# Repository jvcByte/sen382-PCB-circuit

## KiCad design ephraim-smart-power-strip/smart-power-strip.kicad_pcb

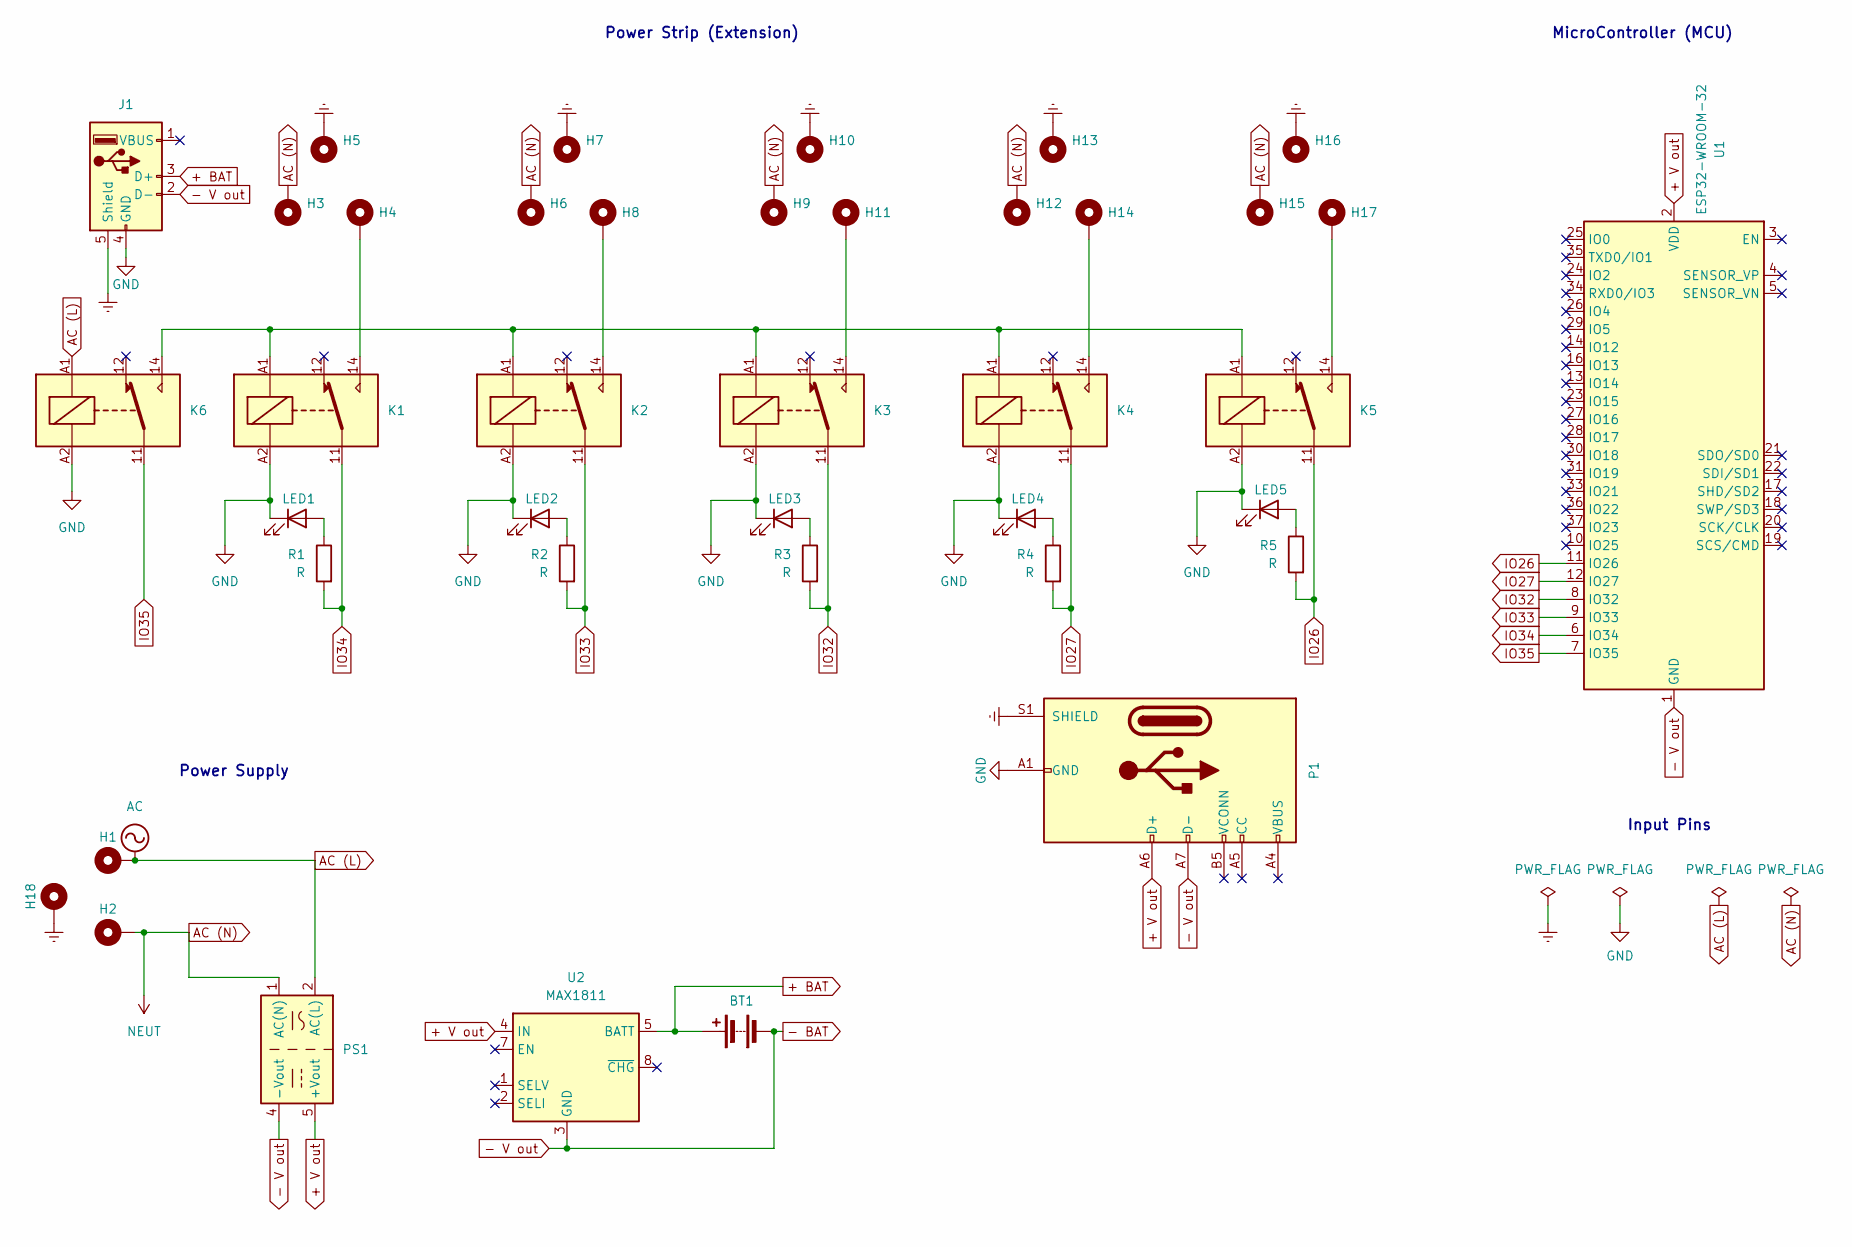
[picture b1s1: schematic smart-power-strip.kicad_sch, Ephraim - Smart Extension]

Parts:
BT1: Battery; BatteryHolder_Keystone_2462_2xAA
H1, H2, H3, H4, H5, H6, H7, H8, H9, H10, H11, H12, H13, H14, H15, H16, H17, H18: MountingHole_Pad; MountingHole_2.2mm_M2_DIN965_Pad
J1: USB_A; USB_A_CNCTech_1001-011-01101_Horizontal
K1, K2, K3, K4, K5, K6: Relay_SPDT; Relay_SPDT_Finder_36.11
LED1, LED2, LED3, LED4, LED5: LED; LED_D4.0mm
P1: USB_C_Plug_USB2.0; USB_C_Plug_Molex_105444
PS1: RAC20-05SK; Converter_ACDC_Recom_RAC20-xxSK_THT
R1, R2, R3, R4, R5: R; R_LDR_4.9x4.2mm_P2.54mm_Vertical
U1: ESP32-WROOM-32
U2: MAX1811; SOIC-8_3.9x4.9mm_P1.27mm

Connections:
+ BAT: BT1.1 (+), J1.3 (D+), U2.5 (BATT)
+ V out: P1.A6 (D+), PS1.5 (+Vout), U1.2 (VDD), U2.4 (IN)
- BAT: BT1.2 (-), J1.2 (D-), P1.A7 (D-), PS1.4 (-Vout), U1.1 (GND), U1.15 (GND), U1.38 (GND), U1.39 (GND), U2.3 (GND), U2.6 (GND)
AC (L): H1.1, K6.A1, PS1.2 (AC(L))
AC (N): H2.1, H3.1, H6.1, H9.1, H12.1, H15.1, PS1.1 (AC(N))
Earth: H5.1, H7.1, H10.1, H13.1, H16.1, H18.1, J1.5 (Shield), P1.S1 (SHIELD)
GND: J1.4 (GND), K1.A2, K2.A2, K3.A2, K4.A2, K5.A2, K6.A2, LED1.1 (K), LED2.1 (K), LED3.1 (K), LED4.1 (K), LED5.1 (K), P1.A1 (GND), P1.A12 (GND), P1.B1 (GND), P1.B12 (GND)
IO26: K5.11, R5.2, U1.11 (IO26)
IO27: K4.11, R4.2, U1.12 (IO27)
IO32: K3.11, R3.2, U1.8 (IO32)
IO33: K2.11, R2.2, U1.9 (IO33)
IO34: K1.11, R1.2, U1.6 (IO34)
IO35: K6.11, U1.7 (IO35)
unnamed: H4.1, K1.14
unnamed: H8.1, K2.14
unnamed: H11.1, K3.14
unnamed: H14.1, K4.14
unnamed: H17.1, K5.14
unnamed: K1.A1, K2.A1, K3.A1, K4.A1, K5.A1, K6.14
unnamed: LED1.2 (A), R1.1
unnamed: LED2.2 (A), R2.1
unnamed: LED3.2 (A), R3.1
unnamed: LED4.2 (A), R4.1
unnamed: LED5.2 (A), R5.1

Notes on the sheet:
Input Pins
MicroController (MCU)
Power Strip (Extension)
Power Supply

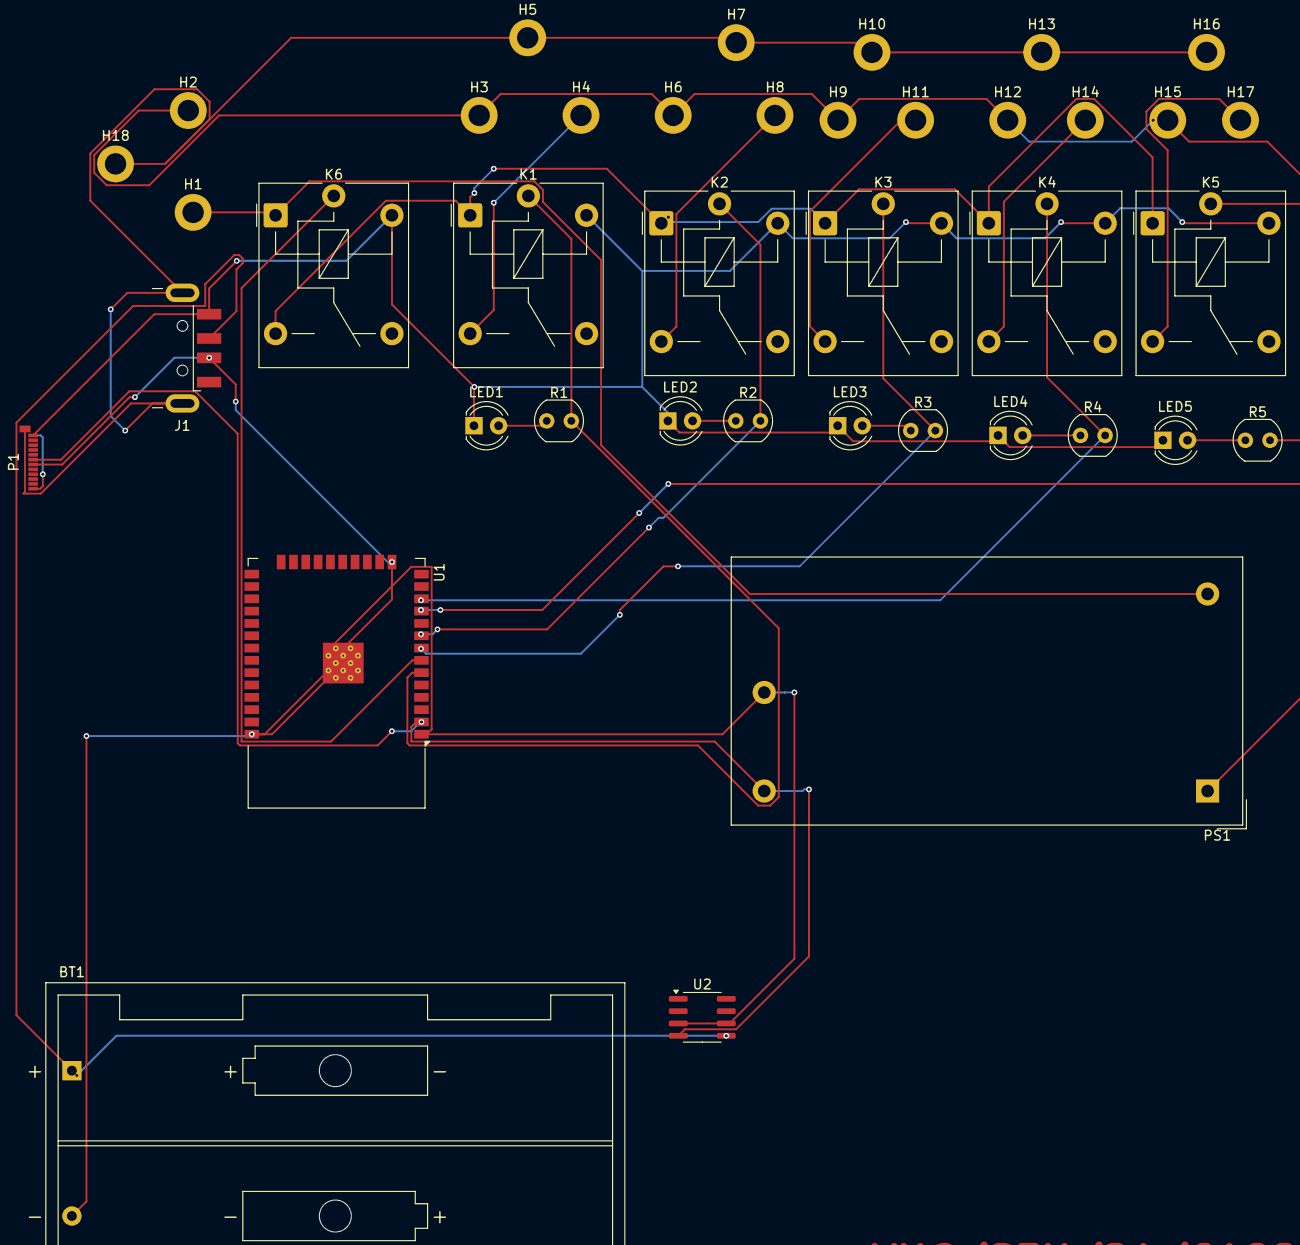
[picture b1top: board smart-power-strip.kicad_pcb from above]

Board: 2 copper layers, 40 parts (0 on the bottom side), 24 nets.

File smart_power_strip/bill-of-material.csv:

"Reference","Value","Footprint","Datasheet","Qty","DNP","Exclude from BOM","Exclude from Board"
"BT1","Battery","Battery:BatteryHolder_Keystone_2462_2xAA","~","1","","",""
"H1,H2,H3,H4,H5,H6,H7,H8,H9,H10,H11,H12,H13,H14,H15,H16,H17,H18","MountingHole_Pad","MountingHole:MountingHole_2.2mm_M2_DIN965_Pad","~","18","","",""
"J1","USB_A","Connector_USB:USB_A_CNCTech_1001-011-01101_Horizontal","~","1","","",""
"K1,K2,K3,K4,K5,K6","Relay_SPDT","Relay_THT:Relay_SPDT_Finder_36.11","~","6","","",""
"LED1,LED2,LED3,LED4,LED5","LED","LED_THT:LED_D4.0mm","~","5","","",""
"P1","USB_C_Plug_USB2.0","Connector_USB:USB_C_Plug_Molex_105444","https://www.usb.org/sites/default/files/documents/usb_type-c.zip","1","","",""
"PS1","RAC20-05SK","Converter_ACDC:Converter_ACDC_Recom_RAC20-xxSK_THT","https://recom-power.com/pdf/Powerline_AC-DC/RAC20-K.pdf","1","","",""
"R1,R2,R3,R4,R5","R","OptoDevice:R_LDR_4.9x4.2mm_P2.54mm_Vertical","~","5","","",""
"U1","ESP32-WROOM-32","RF_Module:ESP32-WROOM-32","https://www.espressif.com/sites/default/files/documentation/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","1","","",""
"U2","MAX1811","Package_SO:SOIC-8_3.9x4.9mm_P1.27mm","https://datasheets.maximintegrated.com/en/ds/MAX1811.pdf","1","","",""

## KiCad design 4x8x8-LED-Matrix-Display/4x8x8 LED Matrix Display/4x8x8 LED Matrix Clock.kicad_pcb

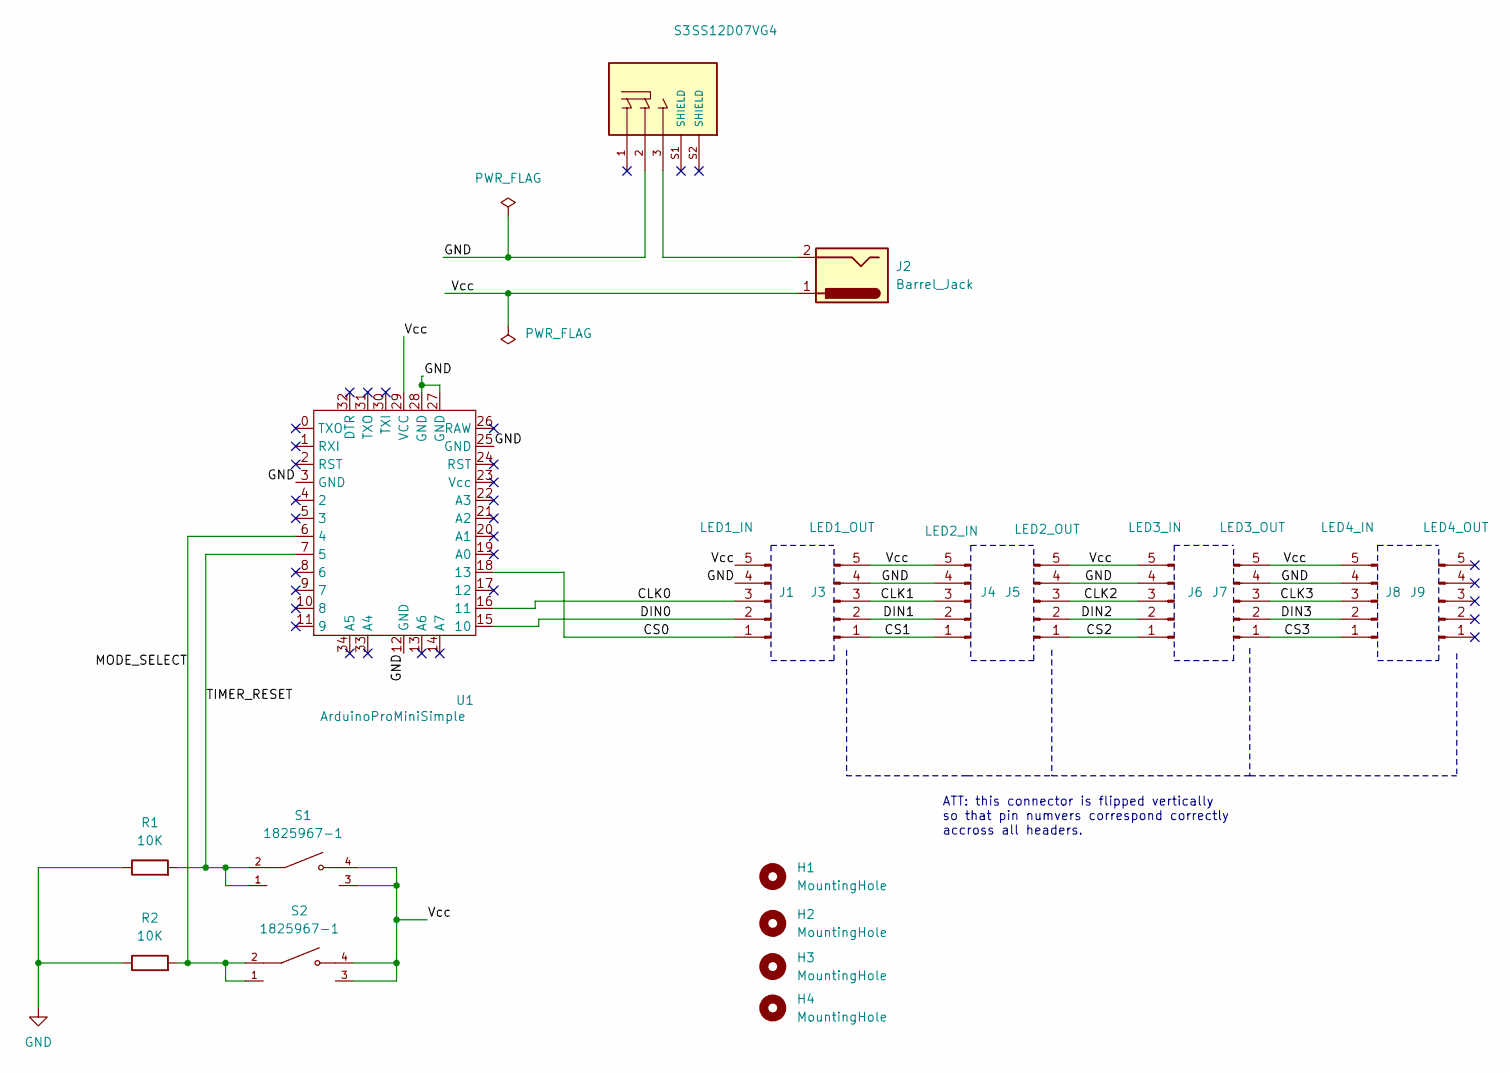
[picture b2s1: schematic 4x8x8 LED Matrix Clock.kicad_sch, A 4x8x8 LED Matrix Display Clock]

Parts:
H1, H2, H3, H4: MountingHole; MountingHole_2.5mm
J1: LED1_IN; PinHeader_1x05_P2.54mm_Vertical
J2: Barrel_Jack; BarrelJack_Horizontal
J3: LED1_OUT; PinHeader_1x05_P2.54mm_Vertical
J4: LED2_IN; PinHeader_1x05_P2.54mm_Vertical
J5: LED2_OUT; PinHeader_1x05_P2.54mm_Vertical
J6: LED3_IN; PinHeader_1x05_P2.54mm_Vertical
J7: LED3_OUT; PinHeader_1x05_P2.54mm_Vertical
J8: LED4_IN; PinHeader_1x05_P2.54mm_Vertical
J9: LED4_OUT; PinHeader_1x05_P2.54mm_Vertical
R1, R2: 10K; R_Axial_DIN0204_L3.6mm_D1.6mm_P7.62mm_Horizontal
S1, S2: 1825967-1; SW_1825967-1
S3: SS12D07VG4; SW_SS12D07VG4; PARTREV 1
U1: ArduinoProMiniSimple; ArduinoProMiniCustom

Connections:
/CLK0: J1.3, U1.16 (11)
/CLK1: J3.3, J4.3
/CLK2: J5.3, J6.3
/CLK3: J7.3, J8.3
/CS0: J1.1, U1.18 (13)
/CS1: J3.1, J4.1
/CS2: J5.1, J6.1
/CS3: J7.1, J8.1
/DIN0: J1.2, U1.15 (10)
/DIN1: J3.2, J4.2
/DIN2: J5.2, J6.2
/DIN3: J7.2, J8.2
/MODE_SELECT: R2.2, S2.1, S2.2, U1.6 (4)
/TIMER_RESET: R1.2, S1.1, S1.2, U1.7 (5)
/Vcc: J1.5, J2.1, J3.5, J4.5, J5.5, J6.5, J7.5, J8.5, S1.3, S1.4, S2.3, S2.4, U1.29 (VCC)
GND: J1.4, J3.4, J4.4, J5.4, J6.4, J7.4, J8.4, R1.1, R2.1, S3.2, U1.3 (GND), U1.12 (GND), U1.25 (GND), U1.27 (GND), U1.28 (GND)
unnamed: J2.2, S3.3

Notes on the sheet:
ATT: this connector is flipped vertically so that pin numvers correspond correctly accross all headers.

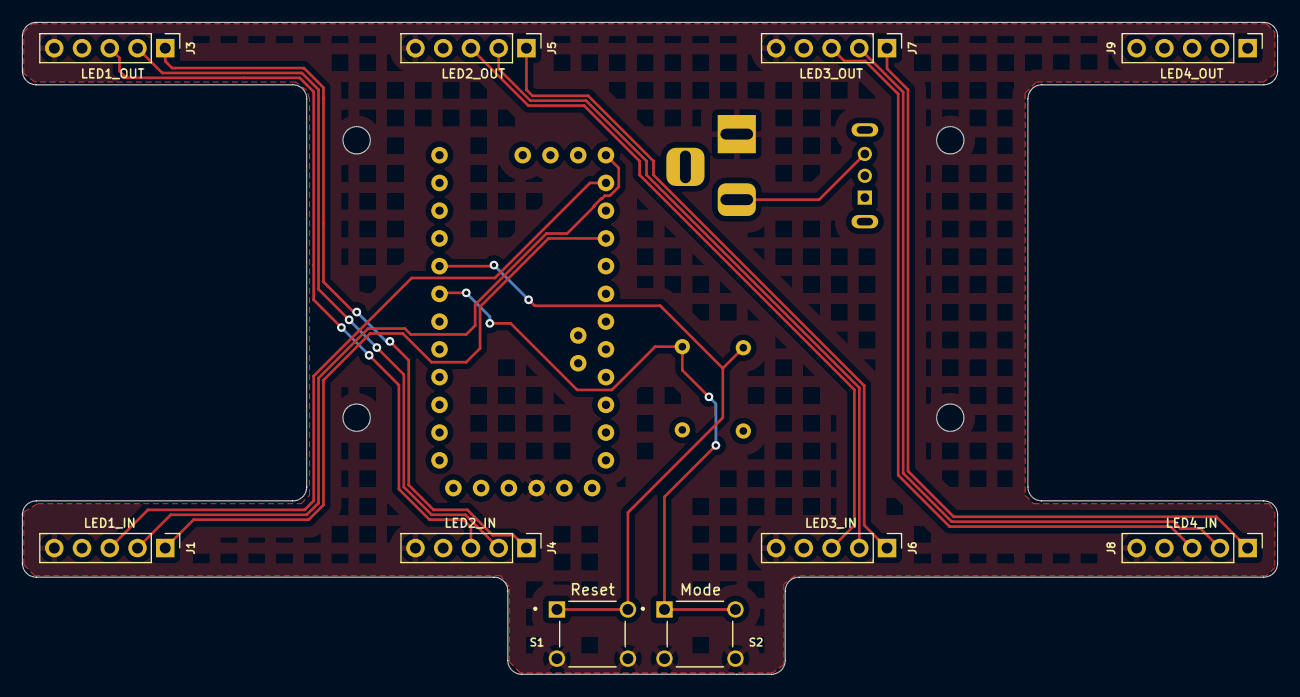
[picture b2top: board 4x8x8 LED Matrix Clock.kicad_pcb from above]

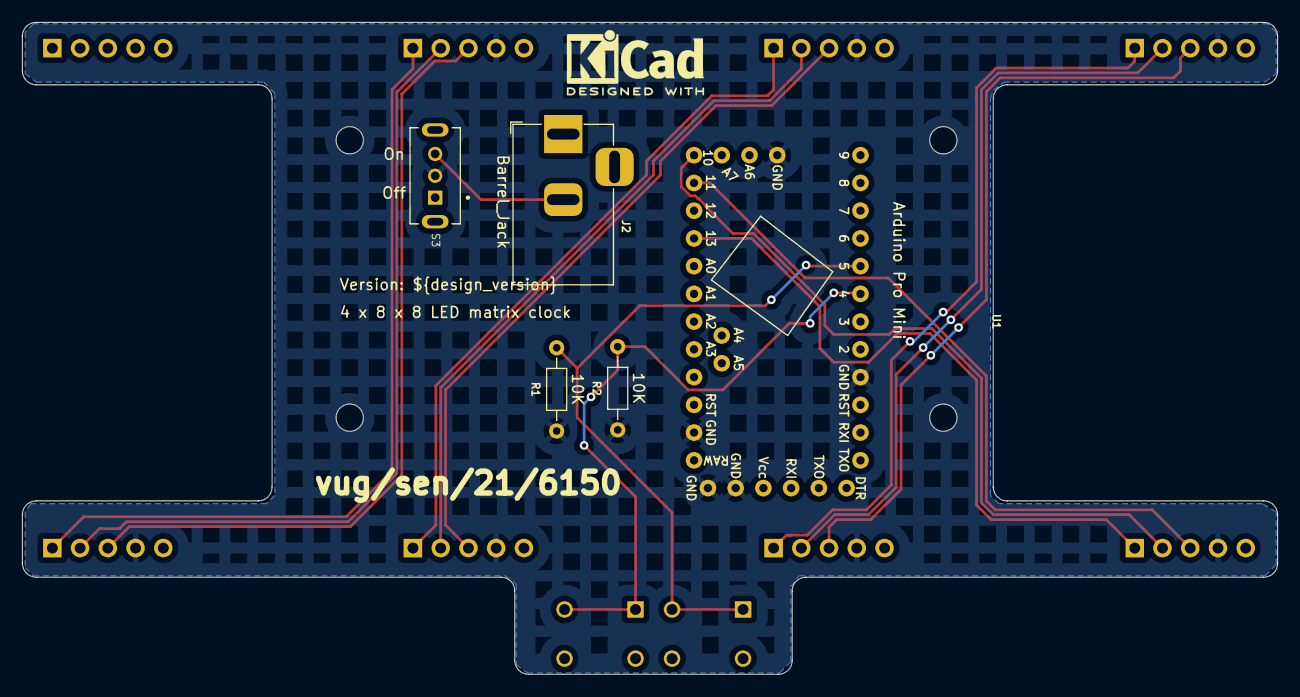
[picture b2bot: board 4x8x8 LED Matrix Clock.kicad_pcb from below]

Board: 2 copper layers, 114.9 x 59.7 mm, 19 parts (5 on the bottom side), 17 nets.

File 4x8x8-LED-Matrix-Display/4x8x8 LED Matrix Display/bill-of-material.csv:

"Reference","Value","Footprint","Datasheet","Qty","DNP","Exclude from BOM","Exclude from Board"
"H1,H2,H3,H4","MountingHole","MountingHole:MountingHole_2.5mm","~","4","","",""
"J1","LED1_IN","Connector_PinHeader_2.54mm:PinHeader_1x05_P2.54mm_Vertical","~","1","","",""
"J2","Barrel_Jack","Connector_BarrelJack:BarrelJack_Horizontal","~","1","","",""
"J3","LED1_OUT","Connector_PinHeader_2.54mm:PinHeader_1x05_P2.54mm_Vertical","~","1","","",""
"J4","LED2_IN","Connector_PinHeader_2.54mm:PinHeader_1x05_P2.54mm_Vertical","~","1","","",""
"J5","LED2_OUT","Connector_PinHeader_2.54mm:PinHeader_1x05_P2.54mm_Vertical","~","1","","",""
"J6","LED3_IN","Connector_PinHeader_2.54mm:PinHeader_1x05_P2.54mm_Vertical","~","1","","",""
"J7","LED3_OUT","Connector_PinHeader_2.54mm:PinHeader_1x05_P2.54mm_Vertical","~","1","","",""
"J8","LED4_IN","Connector_PinHeader_2.54mm:PinHeader_1x05_P2.54mm_Vertical","~","1","","",""
"J9","LED4_OUT","Connector_PinHeader_2.54mm:PinHeader_1x05_P2.54mm_Vertical","~","1","","",""
"R1,R2","10K","Resistor_THT:R_Axial_DIN0204_L3.6mm_D1.6mm_P7.62mm_Horizontal","~","2","","",""
"S1,S2","1825967-1","1825967-1:SW_1825967-1","","2","","",""
"S3","SS12D07VG4","SS12D07VG4:SW_SS12D07VG4","","1","","",""
"U1","ArduinoProMiniSimple","DesktopLibrary:ArduinoProMiniCustom","","1","","",""

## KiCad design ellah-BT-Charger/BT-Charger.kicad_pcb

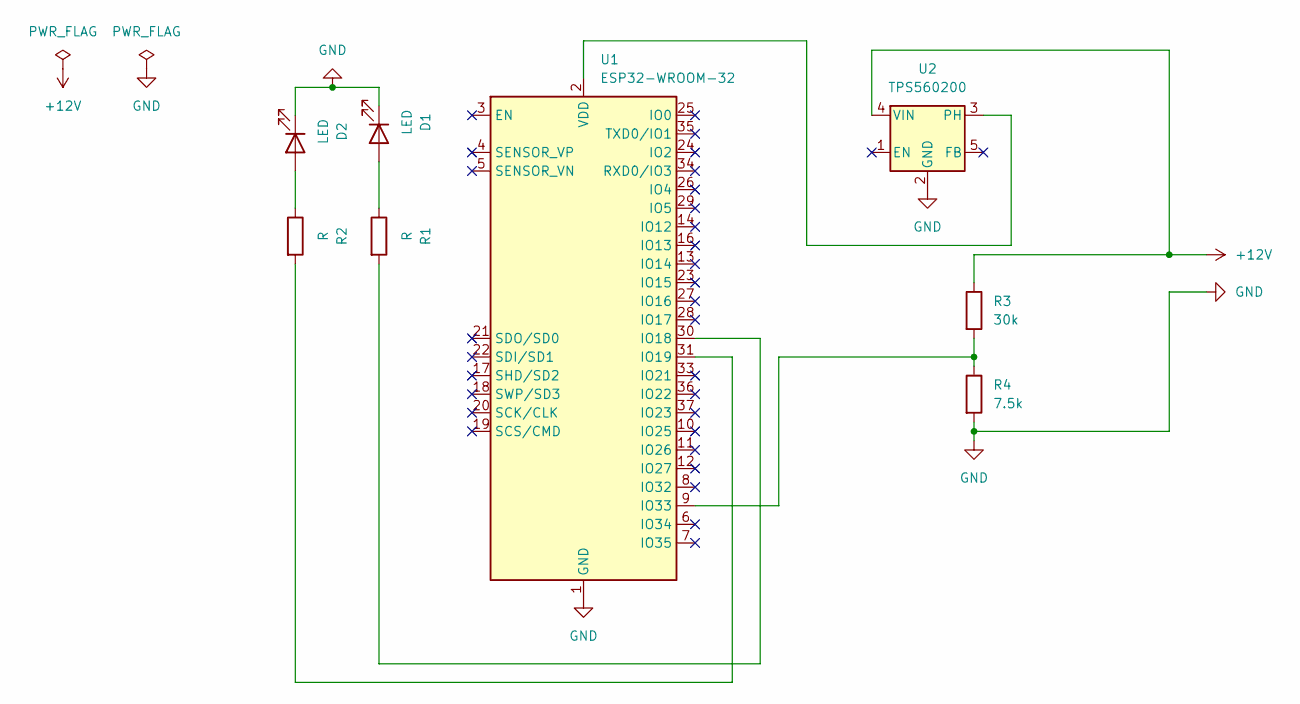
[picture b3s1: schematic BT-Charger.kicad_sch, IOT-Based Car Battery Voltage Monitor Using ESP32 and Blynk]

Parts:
D1, D2: LED; LED_D5.0mm_Horizontal_O6.35mm_Z15.0mm
R1, R2: R; R_0402_1005Metric
R3: 30k; R_Axial_DIN0207_L6.3mm_D2.5mm_P10.16mm_Horizontal
R4: 7.5k; R_Axial_DIN0207_L6.3mm_D2.5mm_P10.16mm_Horizontal
U1: ESP32-WROOM-32
U2: TPS560200; SOT-23-5

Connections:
+12V: R3.1, U2.4 (VIN)
GND: D1.1 (K), D2.1 (K), R4.2, U1.1 (GND), U1.15 (GND), U1.38 (GND), U1.39 (GND), U2.2 (GND)
unnamed: D1.2 (A), R1.1
unnamed: D2.2 (A), R2.1
unnamed: R1.2, U1.30 (IO18)
unnamed: R2.2, U1.31 (IO19)
unnamed: R3.2, R4.1, U1.9 (IO33)
unnamed: U1.2 (VDD), U2.3 (PH)

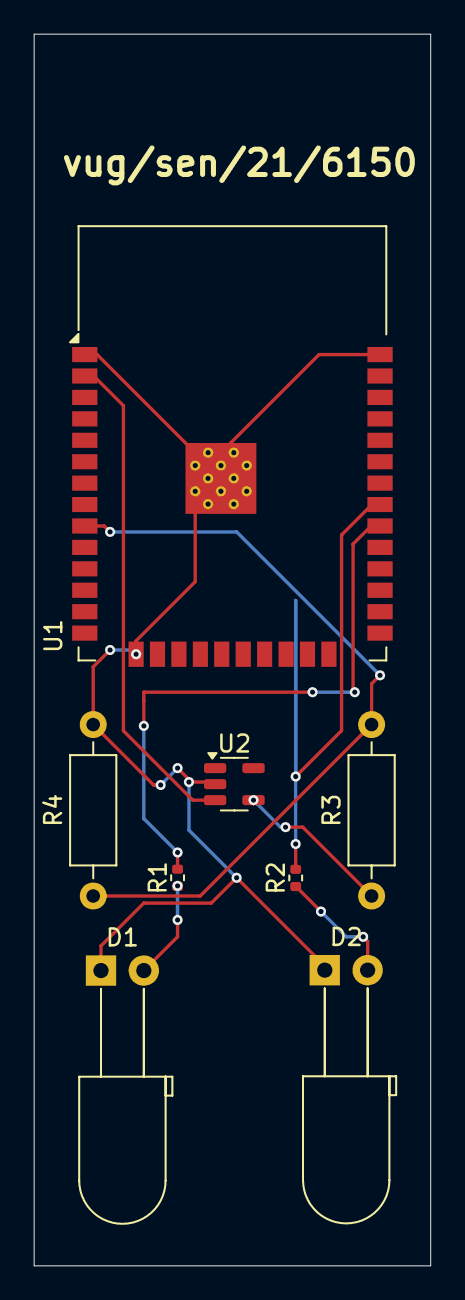
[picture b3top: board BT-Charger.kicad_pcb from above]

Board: 2 copper layers, 23.5 x 73.0 mm, 8 parts (0 on the bottom side), 8 nets.

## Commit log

2025-05-22 added 3 folders
2025-11-08 rename
